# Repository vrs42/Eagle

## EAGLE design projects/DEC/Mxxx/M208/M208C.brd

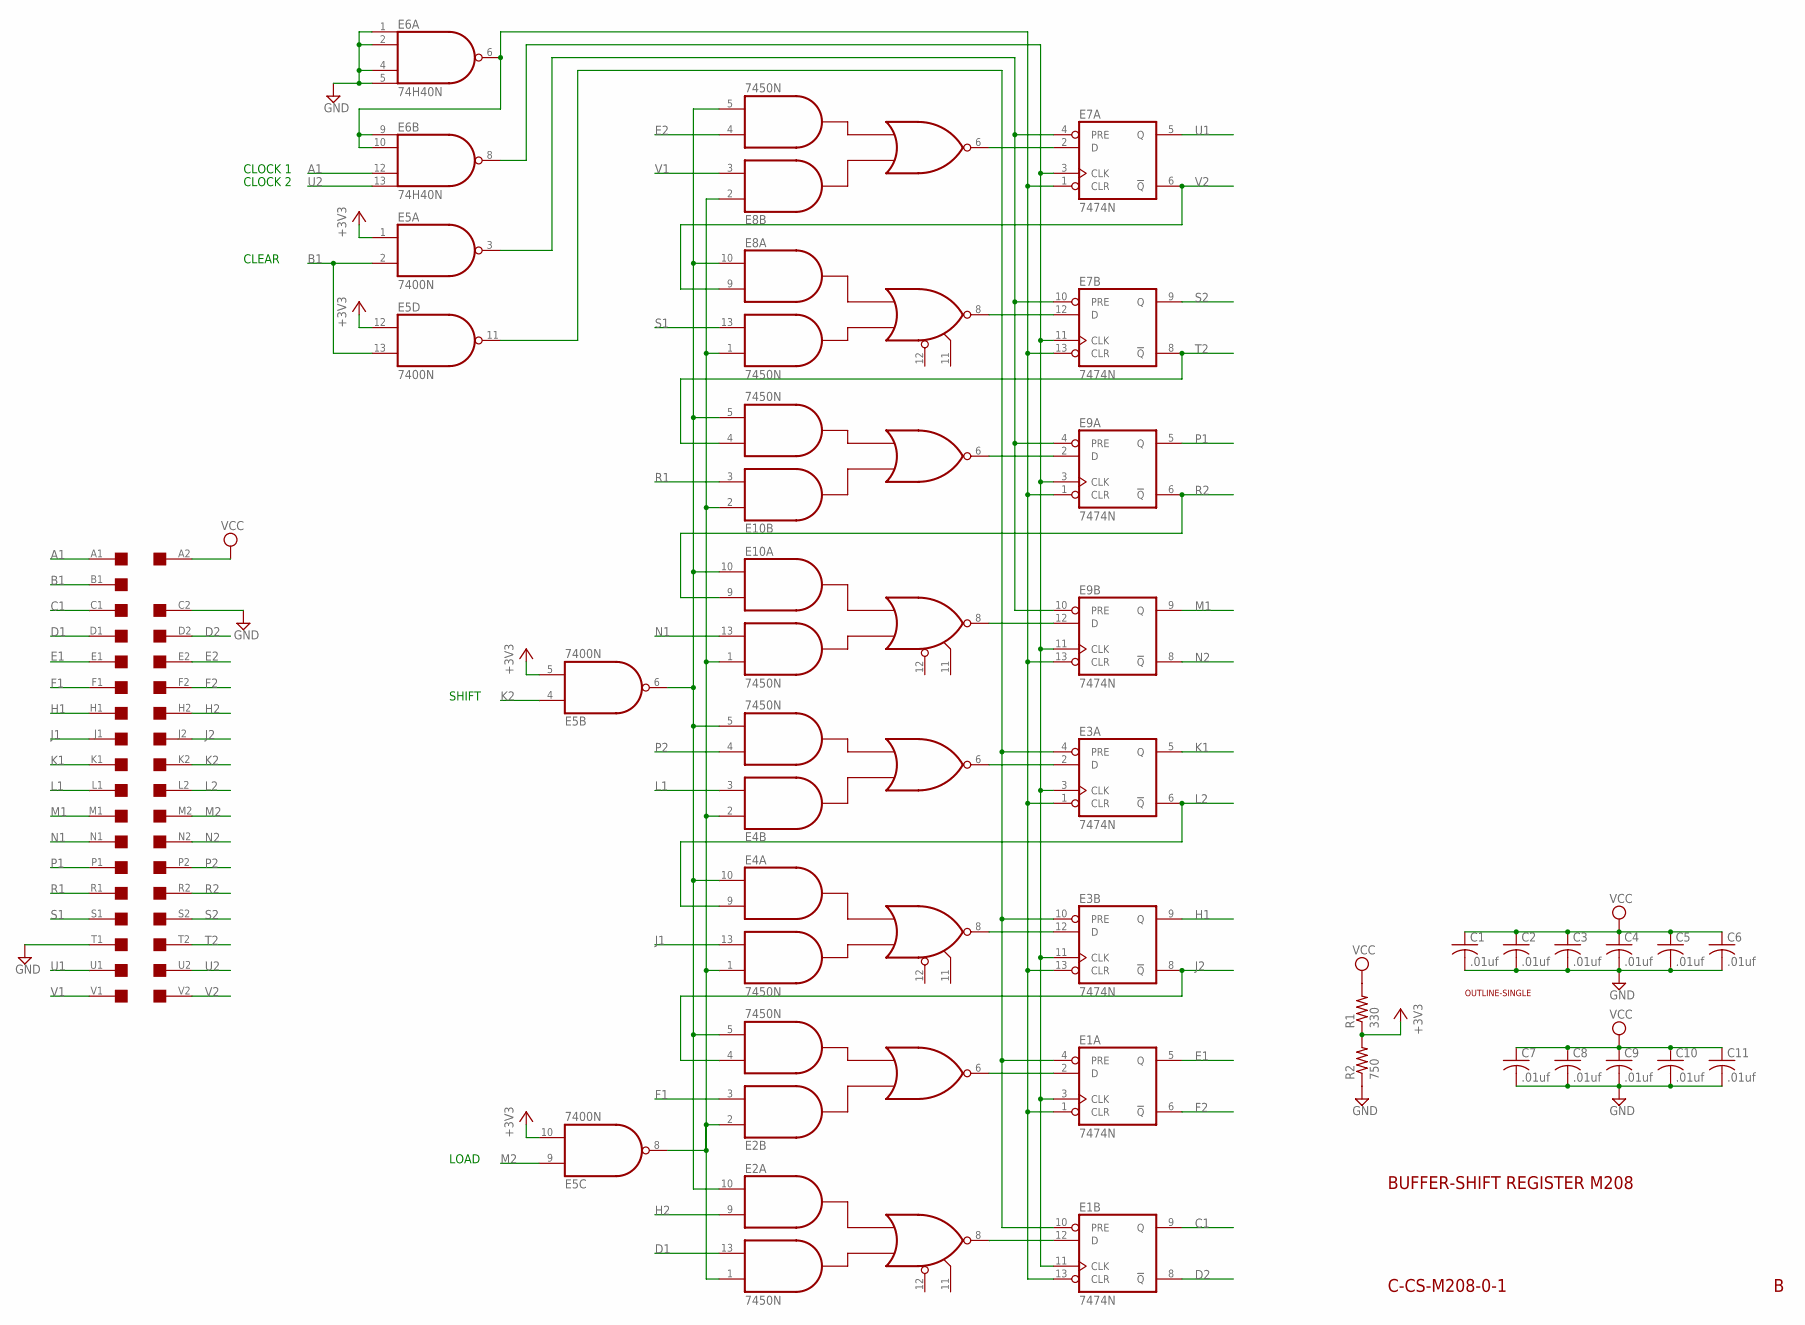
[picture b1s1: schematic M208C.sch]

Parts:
C1, C2, C3, C4, C5, C6, C7, C8, C9, C10, C11: .01uf; C050-025X075
E1, E3, E7, E9: 7474N; DIL14
E2, E4, E8, E10: 7450N; DIL14
E5: 7400N; DIL14
E6: 74H40N; DIL14
R1: 330; 0207/10
R2: 750; 0207/10
U$1: SINGLE; EDGE-CON2
U$4: OUTLINE-SINGLE; SINGLE

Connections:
+3V3: E5.1 (I0), E5.5 (I1), E5.10 (I1), E5.12 (I0), R1.1, R2.2
A1: E6.12 (I2), U$1.A1
B1: E5.2 (I1), E5.13 (I1), U$1.B1
C1: E1.9 (Q), U$1.C1
D1: E2.13 (I3), U$1.D1
D2: E1.8 (!Q), U$1.D2
E1: E1.5 (Q), U$1.E1
E2: E8.4 (I3), U$1.E2
F1: E2.3 (I2), U$1.F1
F2: E1.6 (!Q), U$1.F2
GND: C1.2, C2.2, C3.2, C4.2, C5.2, C6.2, C7.2, C8.2, C9.2, C10.2, C11.2, E1.7 (GND), E2.7 (GND), E3.7 (GND), E4.7 (GND), E5.7 (GND), E6.1 (I0), E6.2 (I1), E6.4 (I2), E6.5 (I3), E6.7 (GND), E7.7 (GND), E8.7 (GND), E9.7 (GND), E10.7 (GND), R2.1, U$1.C2, U$1.T1
H1: E3.9 (Q), U$1.H1
H2: E2.9 (I2), U$1.H2
J1: E4.13 (I3), U$1.J1
J2: E2.4 (I3), E3.8 (!Q), U$1.J2
K1: E3.5 (Q), U$1.K1
K2: E5.4 (I0), U$1.K2
L1: E4.3 (I2), U$1.L1
L2: E3.6 (!Q), E4.9 (I2), U$1.L2
M1: E9.9 (Q), U$1.M1
M2: E5.9 (I0), U$1.M2
N1: E10.13 (I3), U$1.N1
N2: E9.8 (!Q), U$1.N2
unnamed: E7.2 (D), E8.6 (O)
unnamed: E7.12 (D), E8.8 (O)
unnamed: E9.2 (D), E10.6 (O)
unnamed: E9.12 (D), E10.8 (O)
unnamed: E3.2 (D), E4.6 (O)
unnamed: E3.12 (D), E4.8 (O)
unnamed: E1.2 (D), E2.6 (O)
unnamed: E1.12 (D), E2.8 (O)
unnamed: E2.1 (I4), E2.2 (I1), E4.1 (I4), E4.2 (I1), E5.8 (O), E8.1 (I4), E8.2 (I1), E10.1 (I4), E10.2 (I1)
unnamed: E2.5 (I4), E2.10 (I1), E4.5 (I4), E4.10 (I1), E5.6 (O), E8.5 (I4), E8.10 (I1), E10.5 (I4), E10.10 (I1)
unnamed: E1.3 (CLK), E1.11 (CLK), E3.3 (CLK), E3.11 (CLK), E6.8 (O), E7.3 (CLK), E7.11 (CLK), E9.3 (CLK), E9.11 (CLK)
unnamed: E1.1 (CLR), E1.13 (CLR), E3.1 (CLR), E3.13 (CLR), E6.6 (O), E6.9 (I0), E6.10 (I1), E7.1 (CLR), E7.13 (CLR), E9.1 (CLR), E9.13 (CLR)
unnamed: E5.3 (O), E7.4 (PRE), E7.10 (PRE), E9.4 (PRE), E9.10 (PRE)
unnamed: E1.4 (PRE), E1.10 (PRE), E3.4 (PRE), E3.10 (PRE), E5.11 (O)
P1: E9.5 (Q), U$1.P1
P2: E4.4 (I3), U$1.P2
R1: E10.3 (I2), U$1.R1
R2: E9.6 (!Q), E10.9 (I2), U$1.R2
S1: E8.13 (I3), U$1.S1
S2: E7.9 (Q), U$1.S2
T2: E7.8 (!Q), E10.4 (I3), U$1.T2
U1: E7.5 (Q), U$1.U1
U2: E6.13 (I3), U$1.U2
V1: E8.3 (I2), U$1.V1
V2: E7.6 (!Q), E8.9 (I2), U$1.V2
VCC: C1.1, C2.1, C3.1, C4.1, C5.1, C6.1, C7.1, C8.1, C9.1, C10.1, C11.1, E1.14 (VCC), E2.14 (VCC), E3.14 (VCC), E4.14 (VCC), E5.14 (VCC), E6.14 (VCC), E7.14 (VCC), E8.14 (VCC), E9.14 (VCC), E10.14 (VCC), R1.2, U$1.A2

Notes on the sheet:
BUFFER-SHIFT REGISTER M208
C-CS-M208-0-1
CLEAR
CLOCK 1
CLOCK 2
SHIFT
LOAD

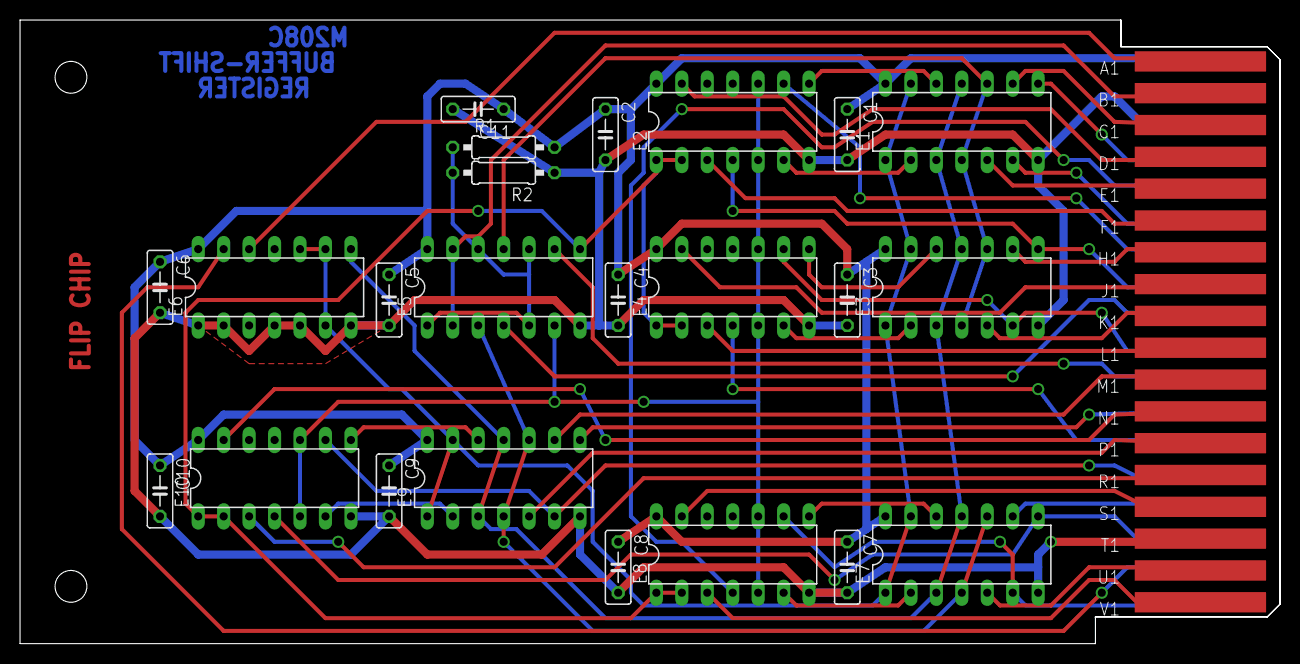
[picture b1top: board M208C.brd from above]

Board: 2 copper layers, 125.7 x 62.2 mm, 25 parts (0 on the bottom side), 49 nets.

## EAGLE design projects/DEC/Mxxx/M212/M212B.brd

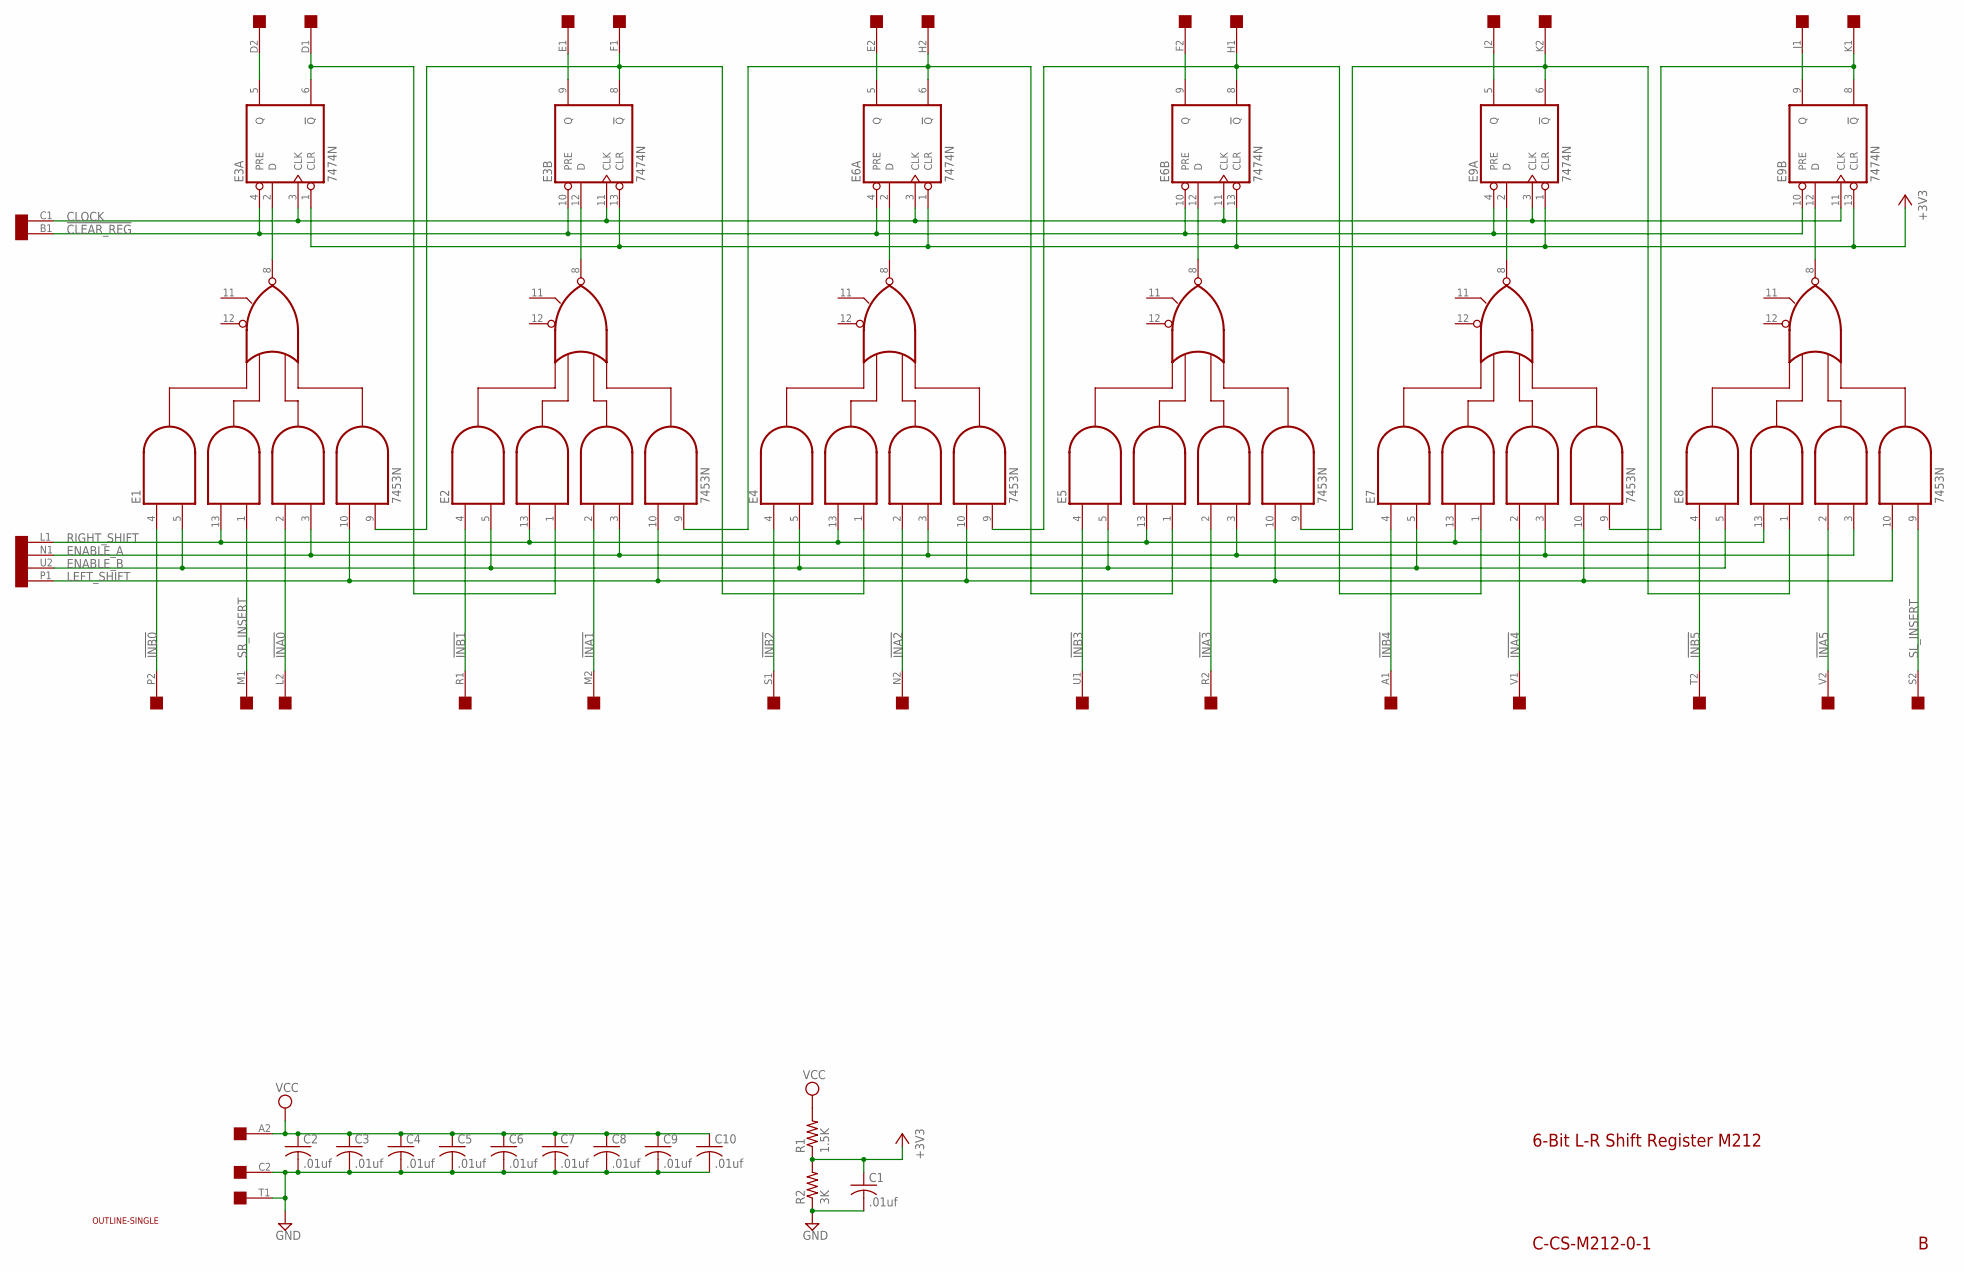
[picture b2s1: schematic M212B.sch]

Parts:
C1: .01uf; C050-025X075
C2, C3, C4, C5, C6, C7, C8, C9, C10: .01uf; C075-032X103
E1, E2, E4, E5, E7, E8: 7453N; DIL14
E3, E6, E9: 7474N; DIL14
EDGE1: EDGE-2CONNECTOR; EDGE-CON2
R1: 1.5K; 0207/10
R2: 3K; 0207/10
U$1: OUTLINE-SINGLE; SINGLE

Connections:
!CLEAR_REG: E3.4 (PRE), E3.10 (PRE), E6.4 (PRE), E6.10 (PRE), E9.4 (PRE), E9.10 (PRE), EDGE1.B1
!INA0: E1.2 (I5), EDGE1.L2
!INA1: E2.2 (I5), EDGE1.M2
!INA2: E4.2 (I5), EDGE1.N2
!INA3: E5.2 (I5), EDGE1.R2
!INA4: E7.2 (I5), EDGE1.V1
!INA5: E8.2 (I5), EDGE1.V2
!INB0: E1.4 (I1), EDGE1.P2
!INB1: E2.4 (I1), EDGE1.R1
!INB2: E4.4 (I1), EDGE1.S1
!INB3: E5.4 (I1), EDGE1.U1
!INB4: E7.4 (I1), EDGE1.A1
!INB5: E8.4 (I1), EDGE1.T2
+3V3: C1.1, E3.1 (CLR), E3.13 (CLR), E6.1 (CLR), E6.13 (CLR), E9.1 (CLR), E9.13 (CLR), R1.1, R2.2
CLOCK: E3.3 (CLK), E3.11 (CLK), E6.3 (CLK), E6.11 (CLK), E9.3 (CLK), E9.11 (CLK), EDGE1.C1
ENABLE_A: E1.3 (I6), E2.3 (I6), E4.3 (I6), E5.3 (I6), E7.3 (I6), E8.3 (I6), EDGE1.N1
ENABLE_B: E1.5 (I2), E2.5 (I2), E4.5 (I2), E5.5 (I2), E7.5 (I2), E8.5 (I2), EDGE1.U2
GND: C1.2, C2.2, C3.2, C4.2, C5.2, C6.2, C7.2, C8.2, C9.2, C10.2, E1.7 (GND), E2.7 (GND), E3.7 (GND), E4.7 (GND), E5.7 (GND), E6.7 (GND), E7.7 (GND), E8.7 (GND), E9.7 (GND), EDGE1.C2, EDGE1.T1, R2.1
LEFT_SHIFT: E1.10 (I7), E2.10 (I7), E4.10 (I7), E5.10 (I7), E7.10 (I7), E8.10 (I7), EDGE1.P1
unnamed: E1.8 (O), E3.2 (D)
unnamed: E2.8 (O), E3.12 (D)
unnamed: E4.8 (O), E6.2 (D)
unnamed: E5.8 (O), E6.12 (D)
unnamed: E7.8 (O), E9.2 (D)
unnamed: E8.8 (O), E9.12 (D)
unnamed: E3.5 (Q), EDGE1.D2
unnamed: E2.1 (I4), E3.6 (!Q), EDGE1.D1
unnamed: E3.9 (Q), EDGE1.E1
unnamed: E1.9 (I8), E3.8 (!Q), E4.1 (I4), EDGE1.F1
unnamed: E6.5 (Q), EDGE1.E2
unnamed: E2.9 (I8), E5.1 (I4), E6.6 (!Q), EDGE1.H2
unnamed: E6.9 (Q), EDGE1.F2
unnamed: E4.9 (I8), E6.8 (!Q), E7.1 (I4), EDGE1.H1
unnamed: E9.5 (Q), EDGE1.J2
unnamed: E5.9 (I8), E8.1 (I4), E9.6 (!Q), EDGE1.K2
unnamed: E9.9 (Q), EDGE1.J1
unnamed: E7.9 (I8), E9.8 (!Q), EDGE1.K1
RIGHT_SHIFT: E1.13 (I3), E2.13 (I3), E4.13 (I3), E5.13 (I3), E7.13 (I3), E8.13 (I3), EDGE1.L1
SL_INSERT: E8.9 (I8), EDGE1.S2
SR_INSERT: E1.1 (I4), EDGE1.M1
VCC: C2.1, C3.1, C4.1, C5.1, C6.1, C7.1, C8.1, C9.1, C10.1, E1.14 (VCC), E2.14 (VCC), E3.14 (VCC), E4.14 (VCC), E5.14 (VCC), E6.14 (VCC), E7.14 (VCC), E8.14 (VCC), E9.14 (VCC), EDGE1.A2, R1.2

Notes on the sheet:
6-Bit L-R Shift Register M212
C-CS-M212-0-1

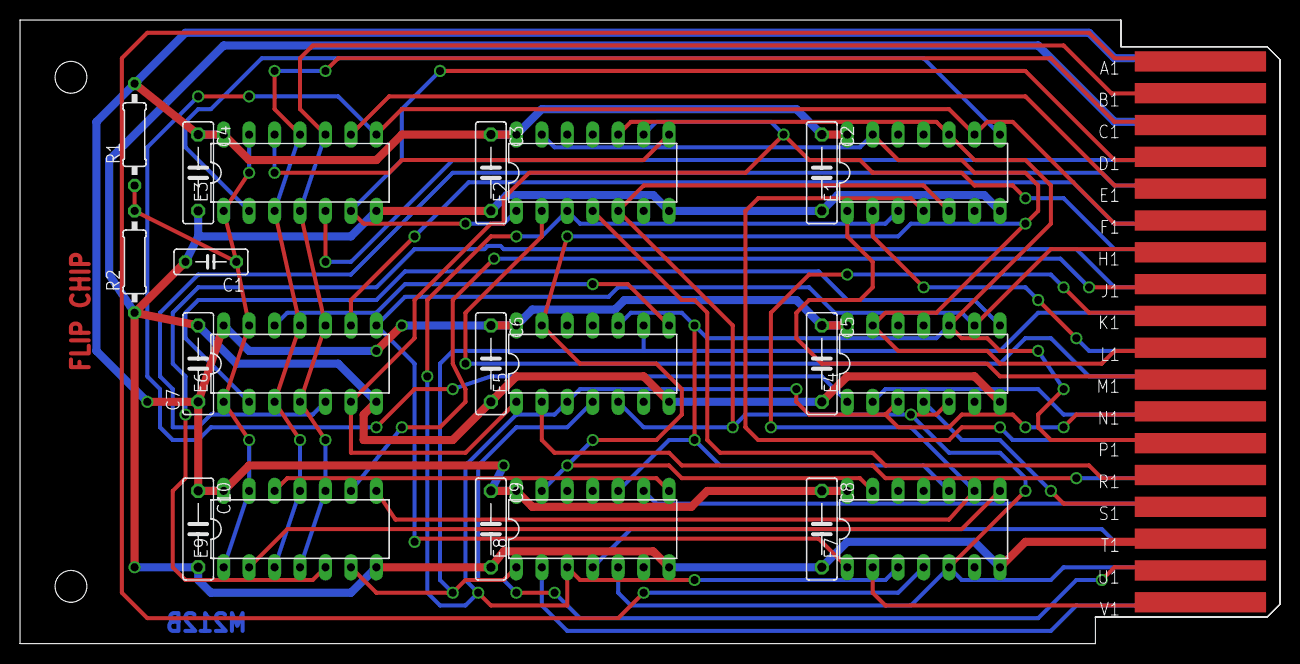
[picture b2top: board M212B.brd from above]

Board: 2 copper layers, 125.7 x 62.2 mm, 23 parts (0 on the bottom side), 41 nets.

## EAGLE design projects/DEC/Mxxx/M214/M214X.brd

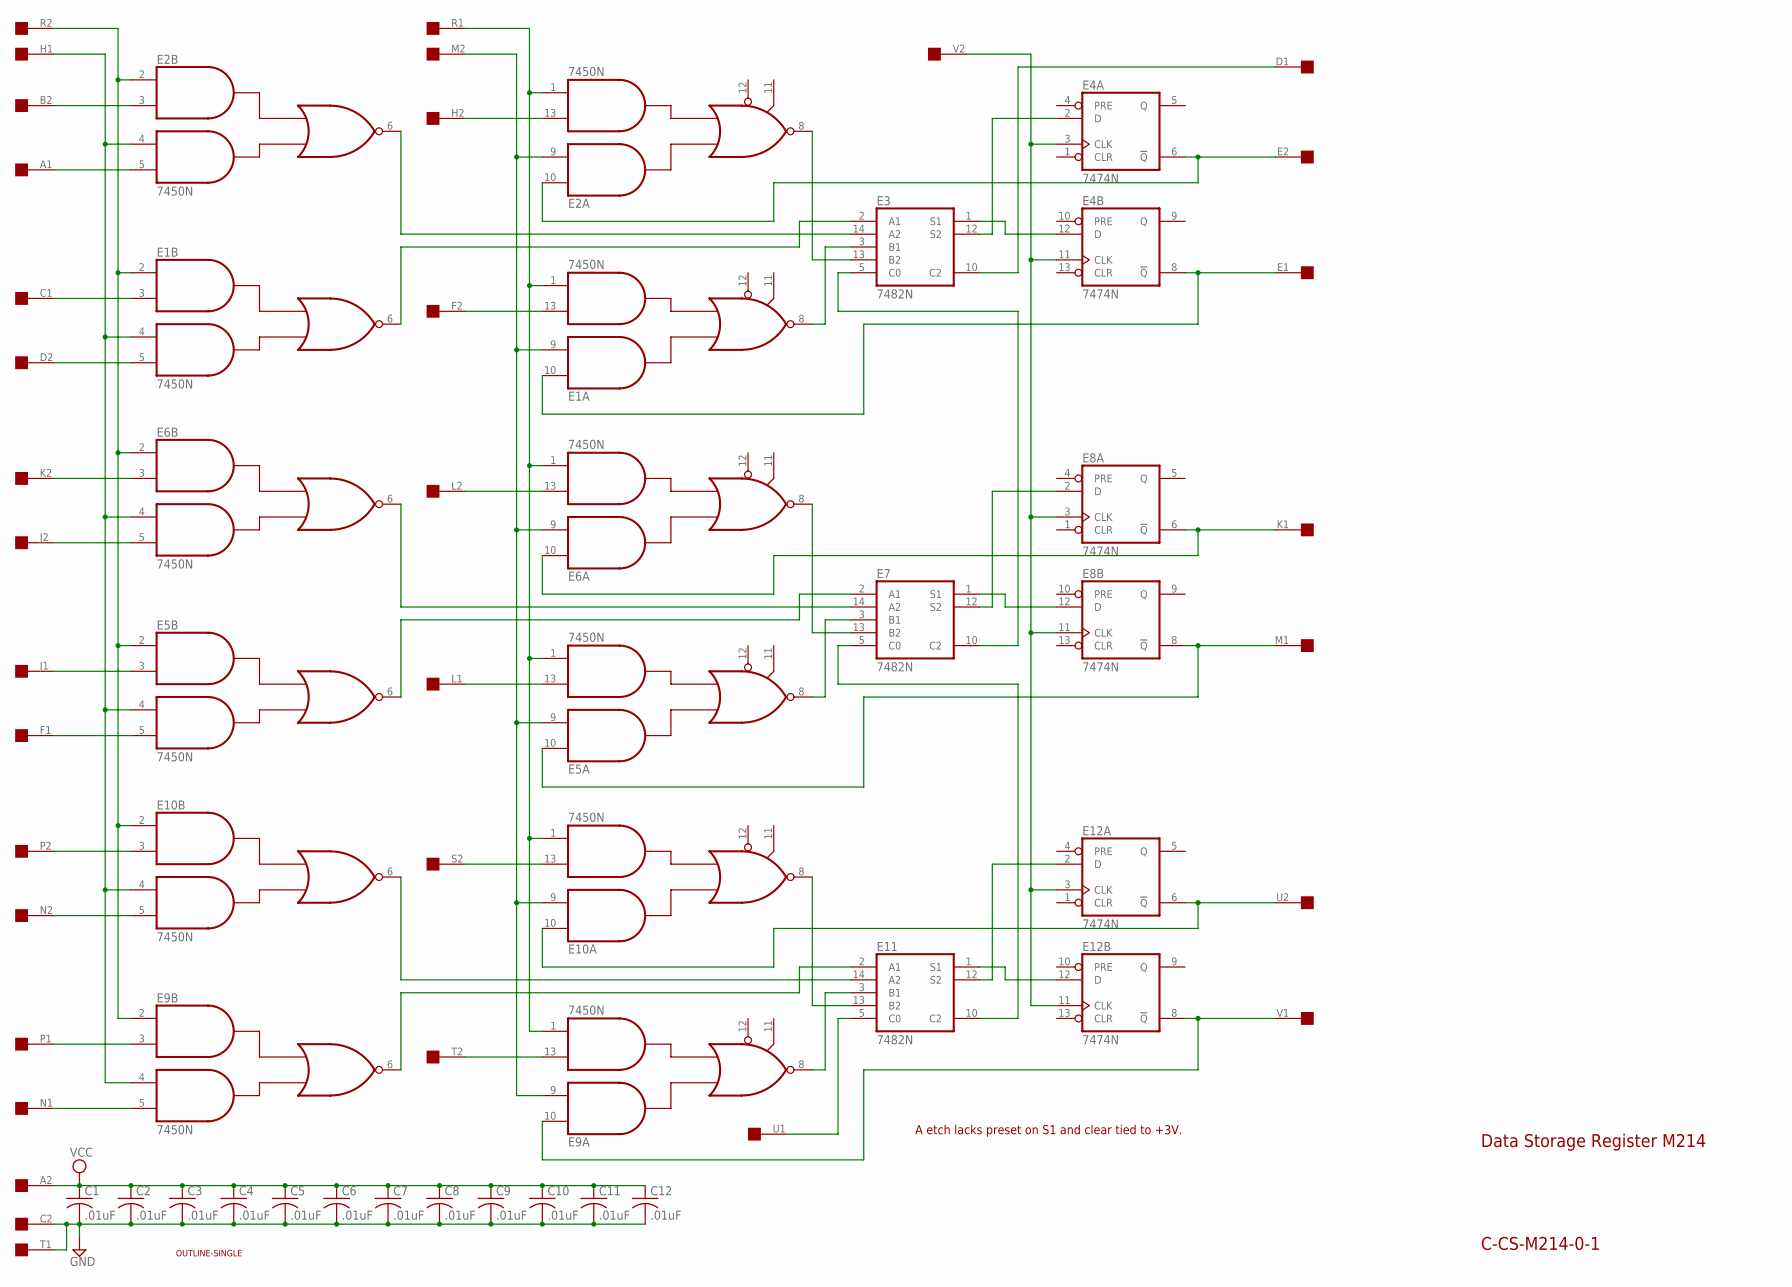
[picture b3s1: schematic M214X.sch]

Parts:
C1, C2, C3, C4, C5, C6, C7, C8, C9, C10, C11, C12: .01uF; C050-025X075
E1, E2, E5, E6, E9, E10: 7450N; DIL14
E3, E7, E11: 7482N; DIL14
E4, E8, E12: 7474N; DIL14
U$1: OUTLINE-SINGLE; SINGLE
U$2: SINGLE; EDGE-CON2

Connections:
GND: C1.2, C2.2, C3.2, C4.2, C5.2, C6.2, C7.2, C8.2, C9.2, C10.2, C11.2, C12.2, E1.7 (GND), E2.7 (GND), E3.11 (GND), E4.7 (GND), E5.7 (GND), E6.7 (GND), E7.11 (GND), E8.7 (GND), E9.7 (GND), E10.7 (GND), E11.11 (GND), E12.7 (GND), U$2.C2, U$2.T1
unnamed: E1.1 (I4), E2.1 (I4), E5.1 (I4), E6.1 (I4), E9.1 (I4), E10.1 (I4), U$2.R1
unnamed: E1.9 (I2), E2.9 (I2), E5.9 (I2), E6.9 (I2), E9.9 (I2), E10.9 (I2), U$2.M2
unnamed: E2.13 (I3), U$2.H2
unnamed: E1.13 (I3), U$2.F2
unnamed: E1.2 (I1), E2.2 (I1), E5.2 (I1), E6.2 (I1), E9.2 (I1), E10.2 (I1), U$2.R2
unnamed: E1.4 (I3), E2.4 (I3), E5.4 (I3), E6.4 (I3), E9.4 (I3), E10.4 (I3), U$2.H1
unnamed: E2.6 (O), E3.14 (A2)
unnamed: E2.8 (O), E3.13 (B2)
unnamed: E1.8 (O), E3.3 (B1)
unnamed: E1.6 (O), E3.2 (A1)
unnamed: E3.5 (C0), E7.10 (C2)
unnamed: E3.12 (S2), E4.2 (D)
unnamed: E3.1 (S1), E4.12 (D)
unnamed: E4.3 (CLK), E4.11 (CLK), E8.3 (CLK), E8.11 (CLK), E12.3 (CLK), E12.11 (CLK), U$2.V2
unnamed: E1.10 (I1), E4.8 (!Q), U$2.E1
unnamed: E2.10 (I1), E4.6 (!Q), U$2.E2
unnamed: E2.3 (I2), U$2.B2
unnamed: E2.5 (I4), U$2.A1
unnamed: E1.3 (I2), U$2.C1
unnamed: E1.5 (I4), U$2.D2
unnamed: E3.10 (C2), U$2.D1
unnamed: E6.13 (I3), U$2.L2
unnamed: E5.13 (I3), U$2.L1
unnamed: E6.6 (O), E7.14 (A2)
unnamed: E6.8 (O), E7.13 (B2)
unnamed: E5.8 (O), E7.3 (B1)
unnamed: E5.6 (O), E7.2 (A1)
unnamed: E7.5 (C0), E11.10 (C2)
unnamed: E7.12 (S2), E8.2 (D)
unnamed: E7.1 (S1), E8.12 (D)
unnamed: E5.10 (I1), E8.8 (!Q), U$2.M1
unnamed: E6.10 (I1), E8.6 (!Q), U$2.K1
unnamed: E6.3 (I2), U$2.K2
unnamed: E6.5 (I4), U$2.J2
unnamed: E5.3 (I2), U$2.J1
unnamed: E5.5 (I4), U$2.F1
unnamed: E10.13 (I3), U$2.S2
unnamed: E9.13 (I3), U$2.T2
unnamed: E10.6 (O), E11.14 (A2)
unnamed: E10.8 (O), E11.13 (B2)
unnamed: E9.8 (O), E11.3 (B1)
unnamed: E9.6 (O), E11.2 (A1)
unnamed: E11.5 (C0), U$2.U1
unnamed: E11.12 (S2), E12.2 (D)
unnamed: E11.1 (S1), E12.12 (D)
unnamed: E9.10 (I1), E12.8 (!Q), U$2.V1
unnamed: E10.10 (I1), E12.6 (!Q), U$2.U2
unnamed: E10.3 (I2), U$2.P2
unnamed: E10.5 (I4), U$2.N2
unnamed: E9.3 (I2), U$2.P1
unnamed: E9.5 (I4), U$2.N1
VCC: C1.1, C2.1, C3.1, C4.1, C5.1, C6.1, C7.1, C8.1, C9.1, C10.1, C11.1, C12.1, E1.14 (VCC), E2.14 (VCC), E3.4 (VCC), E4.14 (VCC), E5.14 (VCC), E6.14 (VCC), E7.4 (VCC), E8.14 (VCC), E9.14 (VCC), E10.14 (VCC), E11.4 (VCC), E12.14 (VCC), U$2.A2

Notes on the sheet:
A etch lacks preset on S1 and clear tied to +3V.
Data Storage Register M214
C-CS-M214-0-1

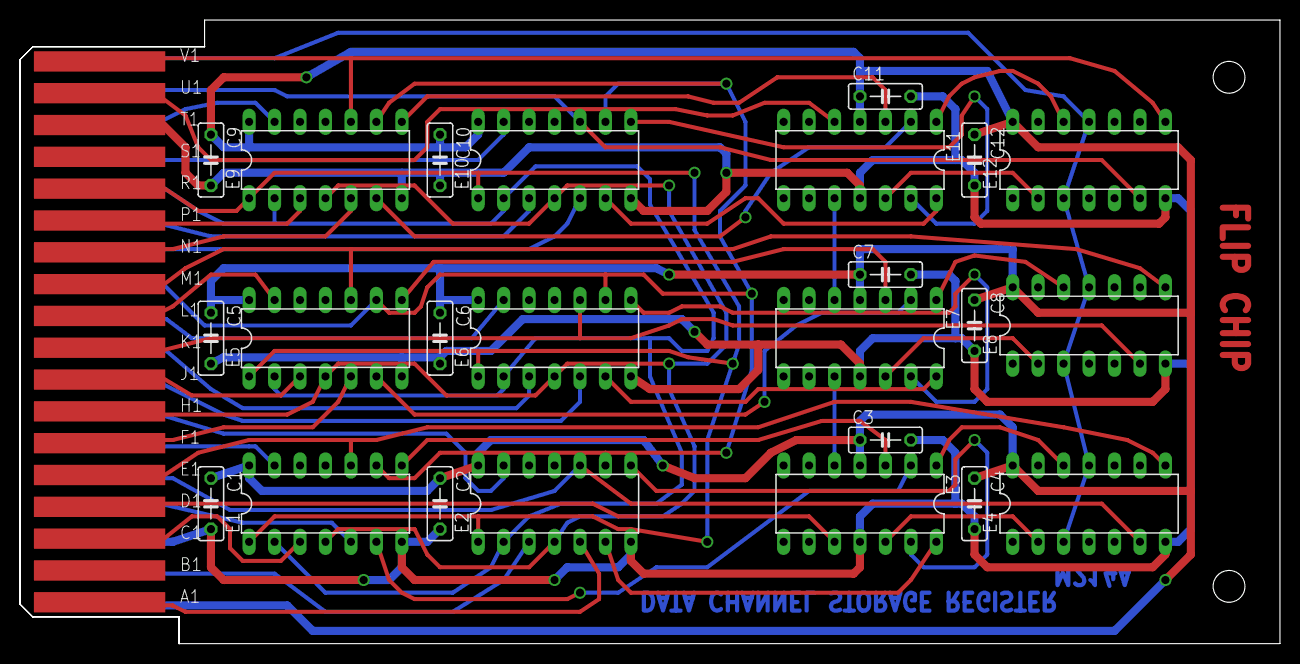
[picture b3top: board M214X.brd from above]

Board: 2 copper layers, 125.7 x 62.2 mm, 26 parts (0 on the bottom side), 53 nets.

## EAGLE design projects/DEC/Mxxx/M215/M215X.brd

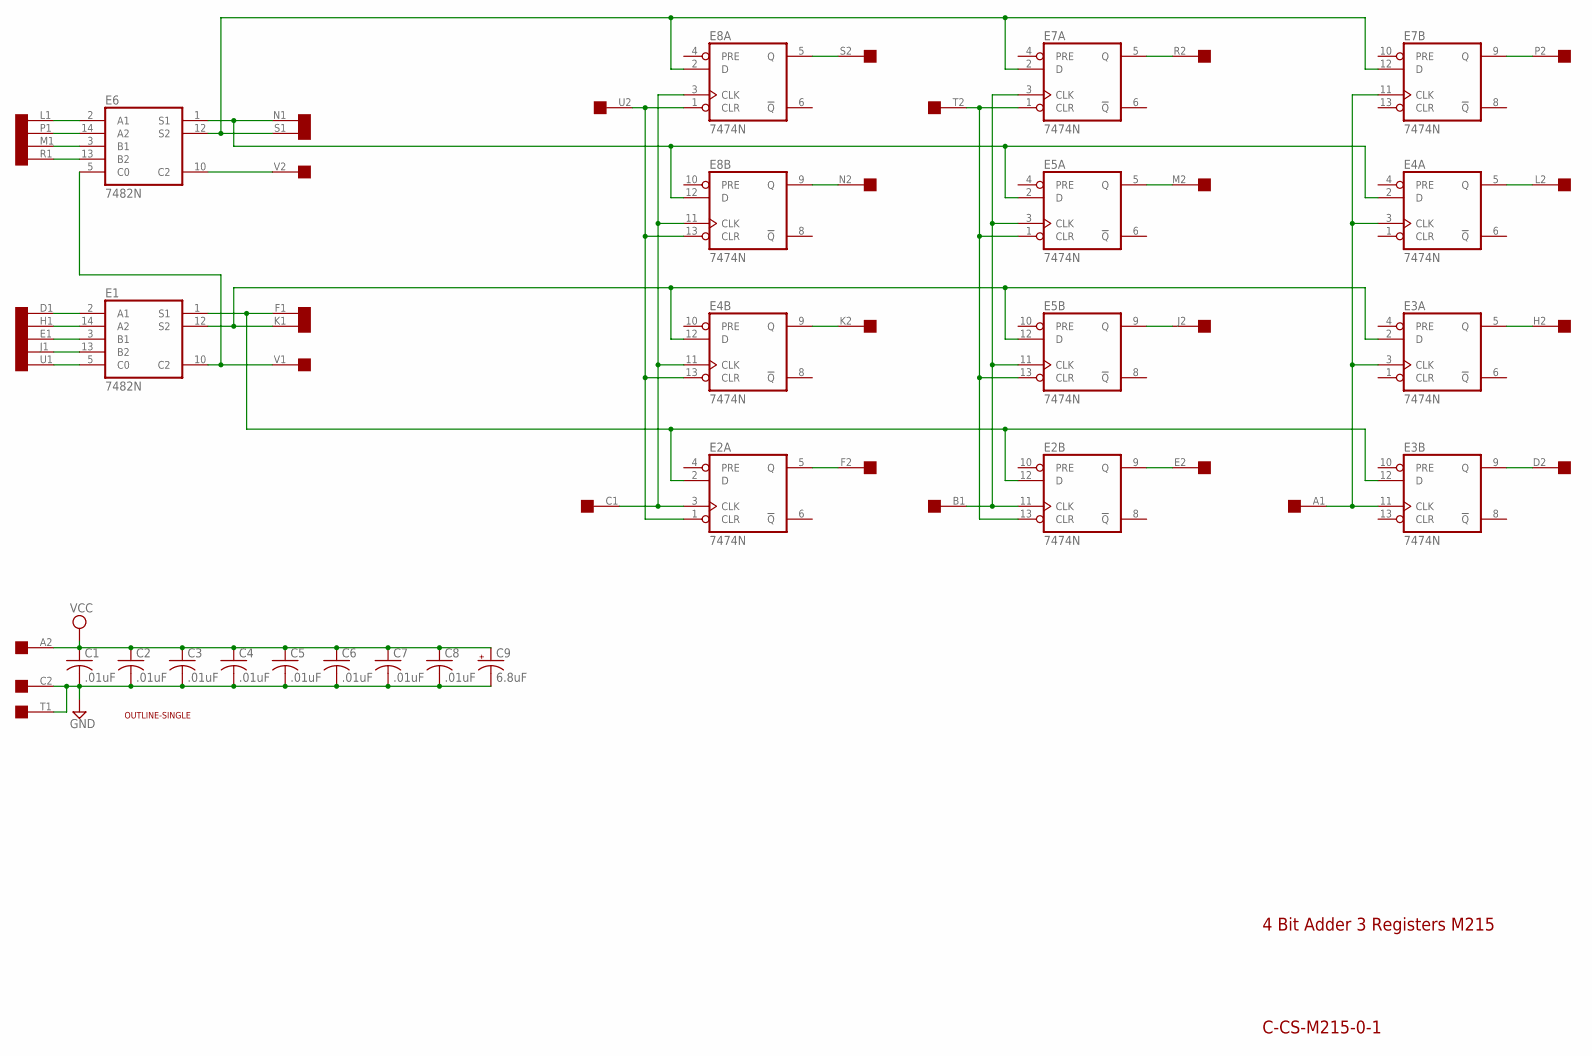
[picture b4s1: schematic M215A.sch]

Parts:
C1, C2, C3, C4, C5, C6, C7, C8: .01uF; C050-025X075
C9: 6.8uF; E12-8
E1, E6: 7482N; DIL14
E2, E3, E4, E5, E7, E8: 7474N; DIL14
U$1: OUTLINE-SINGLE; SINGLE
U$2: SINGLE; EDGE-CON2

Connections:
A1: E3.3 (CLK), E3.11 (CLK), E4.3 (CLK), E7.11 (CLK), U$2.A1
B1: E2.11 (CLK), E5.3 (CLK), E5.11 (CLK), E7.3 (CLK), U$2.B1
C1: E2.3 (CLK), E4.11 (CLK), E8.3 (CLK), E8.11 (CLK), U$2.C1
D1: E1.2 (A1), U$2.D1
D2: E3.9 (Q), U$2.D2
E1: E1.3 (B1), U$2.E1
E2: E2.9 (Q), U$2.E2
F1: E1.1 (S1), E2.2 (D), E2.12 (D), E3.12 (D), U$2.F1
F2: E2.5 (Q), U$2.F2
GND: C1.2, C2.2, C3.2, C4.2, C5.2, C6.2, C7.2, C8.2, C9.-, E1.11 (GND), E2.7 (GND), E3.7 (GND), E4.7 (GND), E5.7 (GND), E6.11 (GND), E7.7 (GND), E8.7 (GND), U$2.C2, U$2.T1
H1: E1.14 (A2), U$2.H1
H2: E3.5 (Q), U$2.H2
J1: E1.13 (B2), U$2.J1
J2: E5.9 (Q), U$2.J2
K1: E1.12 (S2), E3.2 (D), E4.12 (D), E5.12 (D), U$2.K1
K2: E4.9 (Q), U$2.K2
L1: E6.2 (A1), U$2.L1
L2: E4.5 (Q), U$2.L2
M1: E6.3 (B1), U$2.M1
M2: E5.5 (Q), U$2.M2
N1: E4.2 (D), E5.2 (D), E6.1 (S1), E8.12 (D), U$2.N1
N2: E8.9 (Q), U$2.N2
P1: E6.14 (A2), U$2.P1
P2: E7.9 (Q), U$2.P2
R1: E6.13 (B2), U$2.R1
R2: E7.5 (Q), U$2.R2
S1: E6.12 (S2), E7.2 (D), E7.12 (D), E8.2 (D), U$2.S1
S2: E8.5 (Q), U$2.S2
T2: E2.13 (CLR), E5.1 (CLR), E5.13 (CLR), E7.1 (CLR), U$2.T2
U1: E1.5 (C0), U$2.U1
U2: E2.1 (CLR), E4.13 (CLR), E8.1 (CLR), E8.13 (CLR), U$2.U2
V1: E1.10 (C2), E6.5 (C0), U$2.V1
V2: E6.10 (C2), U$2.V2
VCC: C1.1, C2.1, C3.1, C4.1, C5.1, C6.1, C7.1, C8.1, C9.+, E1.4 (VCC), E2.14 (VCC), E3.14 (VCC), E4.14 (VCC), E5.14 (VCC), E6.4 (VCC), E7.14 (VCC), E8.14 (VCC), U$2.A2

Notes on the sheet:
C-CS-M215-0-1
4 Bit Adder 3 Registers M215

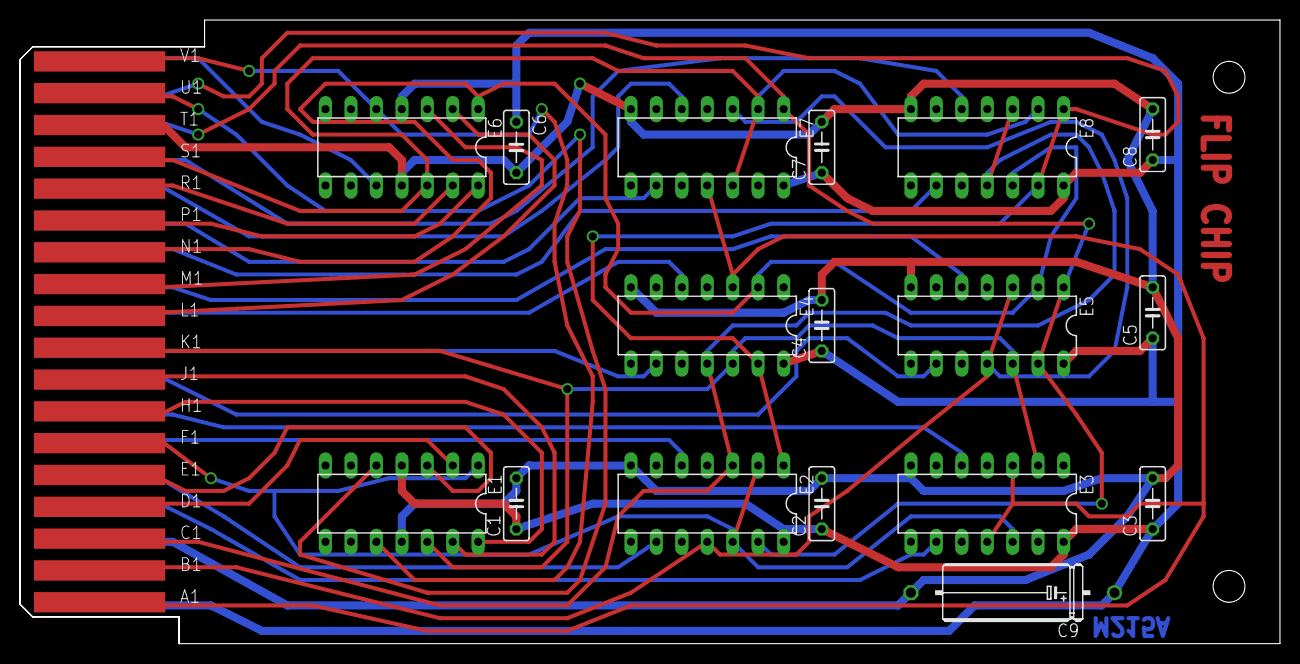
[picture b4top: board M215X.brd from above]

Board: 2 copper layers, 125.7 x 62.2 mm, 19 parts (0 on the bottom side), 34 nets.

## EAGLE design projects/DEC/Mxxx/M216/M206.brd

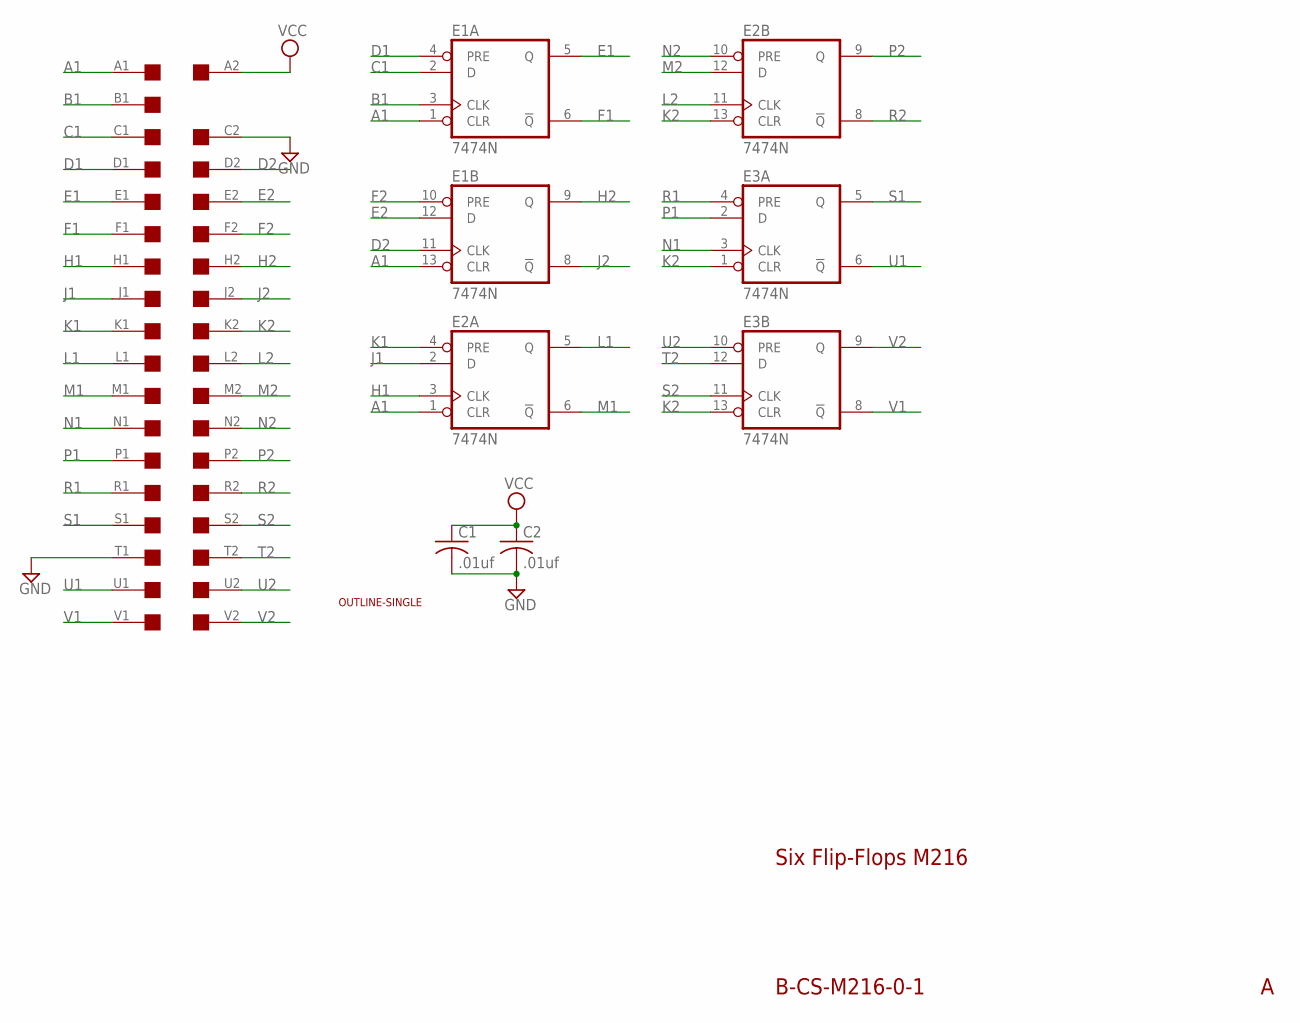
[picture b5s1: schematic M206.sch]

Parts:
C1, C2: .01uf; C050-025X075
E1, E2, E3: 7474N; DIL14
U$1: OUTLINE-SINGLE; SINGLE
U$4: SINGLE; EDGE-CON2

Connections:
A1: E1.1 (CLR), E1.13 (CLR), E2.1 (CLR), U$4.A1
B1: E1.3 (CLK), U$4.B1
C1: E1.2 (D), U$4.C1
D1: E1.4 (PRE), U$4.D1
D2: E1.11 (CLK), U$4.D2
E1: E1.5 (Q), U$4.E1
E2: E1.12 (D), U$4.E2
F1: E1.6 (!Q), U$4.F1
F2: E1.10 (PRE), U$4.F2
GND: C1.2, C2.2, E1.7 (GND), E2.7 (GND), E3.7 (GND), U$4.C2, U$4.T1
H1: E2.3 (CLK), U$4.H1
H2: E1.9 (Q), U$4.H2
J1: E2.2 (D), U$4.J1
J2: E1.8 (!Q), U$4.J2
K1: E2.4 (PRE), U$4.K1
K2: E2.13 (CLR), E3.1 (CLR), E3.13 (CLR), U$4.K2
L1: E2.5 (Q), U$4.L1
L2: E2.11 (CLK), U$4.L2
M1: E2.6 (!Q), U$4.M1
M2: E2.12 (D), U$4.M2
N1: E3.3 (CLK), U$4.N1
N2: E2.10 (PRE), U$4.N2
P1: E3.2 (D), U$4.P1
P2: E2.9 (Q), U$4.P2
R1: E3.4 (PRE), U$4.R1
R2: E2.8 (!Q), U$4.R2
S1: E3.5 (Q), U$4.S1
S2: E3.11 (CLK), U$4.S2
T2: E3.12 (D), U$4.T2
U1: E3.6 (!Q), U$4.U1
U2: E3.10 (PRE), U$4.U2
V1: E3.8 (!Q), U$4.V1
V2: E3.9 (Q), U$4.V2
VCC: C1.1, C2.1, E1.14 (VCC), E2.14 (VCC), E3.14 (VCC), U$4.A2

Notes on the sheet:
B-CS-M216-0-1
Six Flip-Flops M216

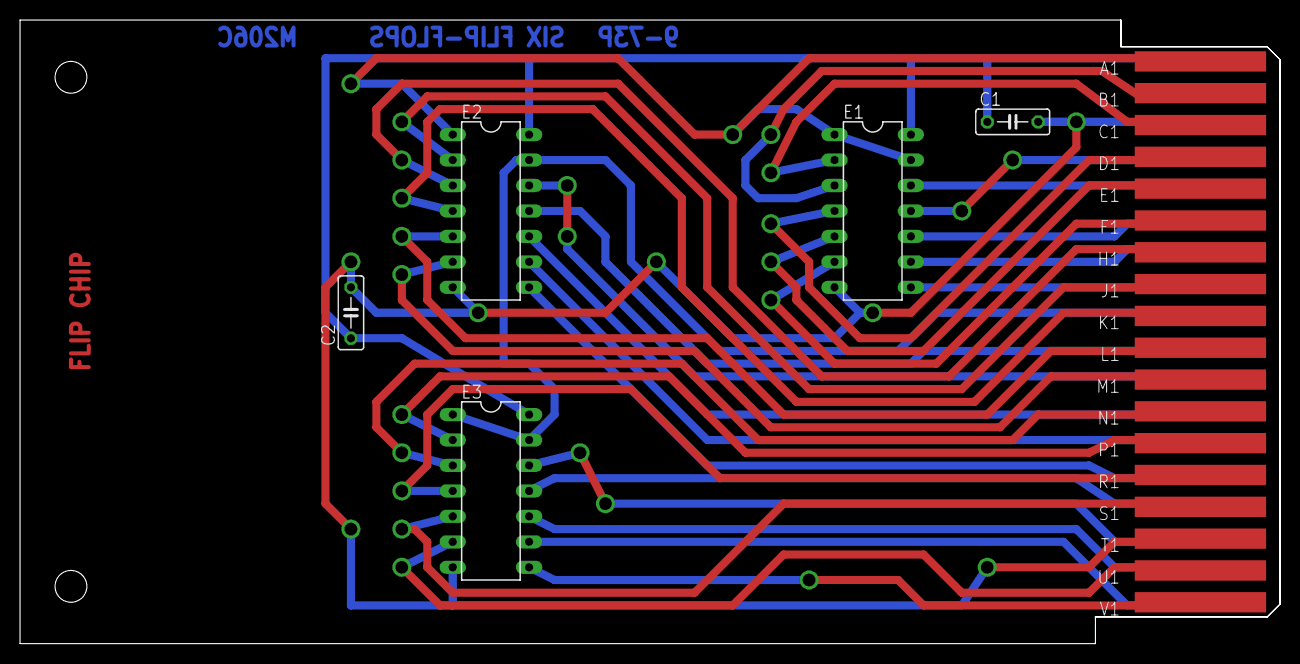
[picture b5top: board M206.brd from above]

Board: 2 copper layers, 125.7 x 62.2 mm, 7 parts (0 on the bottom side), 34 nets.
